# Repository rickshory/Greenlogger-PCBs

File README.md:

# Greenlogger-PCBs
Greenlogger printed circuit board files, the main board and the GPS board

For an overview:

* https://rickshory.wordpress.com/2017/08/24/greenlogger/

Format is EagleCAD schematic and board layout
 
 ## Contact
#### Developer/Company
* Project of: http://www.rickshory.com/
* e-mail: rickshory@gmail.com

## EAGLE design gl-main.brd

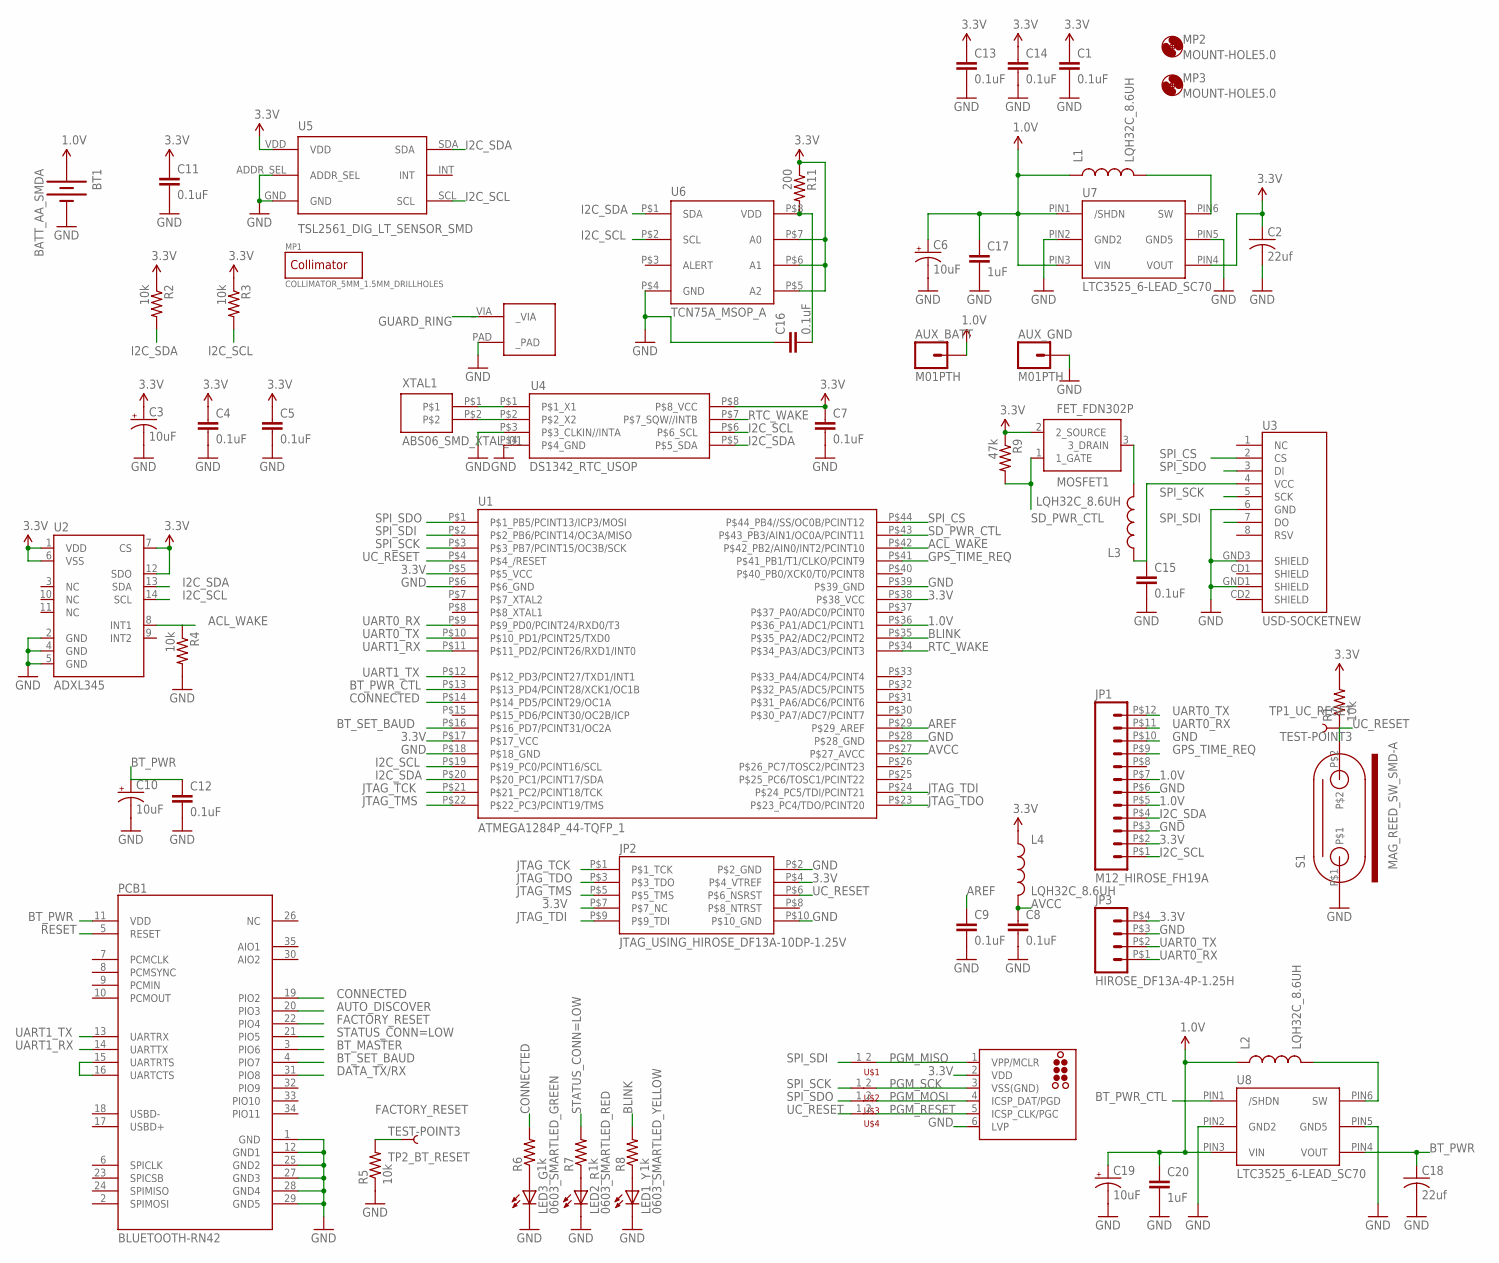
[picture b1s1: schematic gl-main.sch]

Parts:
AUX_BATT: M01PTH; 1X01
AUX_GND: M01PTH; 1X01
BT1: BATT_AA_SMDA; BATT_AA_SMD
C1, C4, C5, C7, C8, C9, C11, C12, C13, C14, C15, C16: 0.1uF; 0402-CAP
C2, C18: 22uf; C1210K
C3, C6, C10, C19: 10uF; EIA3216
C17, C20: 1uF; 0603-CAP
J1: TC2030-MCP-NL
JP1: M12_HIROSE_FH19A; HIROSE_FH19_12POS
JP2: JTAG_USING_HIROSE_DF13A-10DP-1.25V; 10PIN_MALE_HDR_DBL-ROW_HIROSE_D13
JP3: HIROSE_DF13A-4P-1.25H
L1, L2, L3, L4: LQH32C_8.6UH; 1210_SIZE_INDUCTOR
LED1_Y: 0603_SMARTLED_YELLOW; 0603_SMARTLED
LED2_R: 0603_SMARTLED_RED; 0603_SMARTLED
LED3_G: 0603_SMARTLED_GREEN; 0603_SMARTLED
MOSFET1: FET_FDN302P; SUPERSOT-3
MP1: COLLIMATOR_5MM_1.5MM_DRILLHOLES
MP2, MP3: MOUNT-HOLE5.0; 5,0
PCB1: BLUETOOTH-RN42; RN41
R1, R2, R3, R4, R5: 10k; 0402-RES
R6, R7, R8: 1k; 0402-RES
R9: 47k; 0402-RES
R11: 200; 0402-RES
S1: MAG_REED_SW_SMD-A; MAG_REED_SW_SMD_GULL-WING
TP1_UC_RESET, TP2_BT_RESET: TEST-POINT3; PAD.03X.03
U1: ATMEGA1284P_44-TQFP_1; 44-TQFP
U2: ADXL345; LGA14
U3: USD-SOCKETNEW; MICRO-SD-SOCKET-PP
U4: DS1342_RTC_USOP; 8-MICROMAX
U5: TSL2561_DIG_LT_SENSOR_SMD; 6_PAD_FLAT_NO-LEAD
U6: TCN75A_MSOP_A; MSOP-8
U7, U8: LTC3525_6-LEAD_SC70; SC70
U$1, U$2, U$3, U$4: SHORT_8MIL8MIL; SHORT_8MIL
W1: 2-SIGNAL_VIA_AND_PAD_01; 2_SIGNALS_VIA_AND_PAD
XTAL1: ABS06_SMD_XTAL_01; ABS06

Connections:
1.0V: AUX_BATT.1, BT1.P$1 (+), C6.A (+), C17.1, C19.A (+), C20.1, JP1.P$5 (5), JP1.P$7 (7), L1.P$1 (1), L2.P$1 (1), U1.P$36 (P$36_PA1/ADC1/PCINT1), U7.PIN1 (/SHDN), U7.PIN3 (VIN), U8.PIN3 (VIN)
3.3V: C1.1, C2.1, C3.A (+), C4.1, C5.1, C7.1, C11.1, C13.1, C14.1, J1.2 (VDD), JP1.P$2 (2), JP2.P$4 (P$4_VTREF), JP2.P$7 (P$7_NC), JP3.P$4 (4), L4.P$1 (1), MOSFET1.2 (2_SOURCE), R1.2, R2.1, R3.1, R9.1, R11.1, U1.P$5 (P$5_VCC), U1.P$17 (P$17_VCC), U1.P$38 (P$38_VCC), U2.1 (VDD), U2.6 (VSS), U2.7 (CS), U2.12 (SDO), U4.P$8 (P$8_VCC), U5.VDD, U6.P$5 (A2), U6.P$6 (A1), U6.P$7 (A0), U7.PIN4 (VOUT)
ACL_WAKE: R4.1, U1.P$42 (P$42_PB2/AIN0/INT2/PCINT10), U2.8 (INT1)
AREF: C9.1, U1.P$29 (P$29_AREF)
AUTO_DISCOVER: PCB1.20 (PIO3)
AVCC: C8.1, L4.P$2 (2), U1.P$27 (P$27_AVCC)
BLINK: R8.2, U1.P$35 (P$35_PA2/ADC2/PCINT2)
BT_MASTER: PCB1.3 (PIO6)
BT_PWR: C10.A (+), C12.1, C18.1, PCB1.11 (VDD), U8.PIN4 (VOUT)
BT_PWR_CTL: U1.P$13 (P$13_PD4/PCINT28/XCK1/OC1B), U8.PIN1 (/SHDN)
BT_SET_BAUD: PCB1.4 (PIO7), U1.P$16 (P$16_PD7/PCINT31/OC2A)
CONNECTED: PCB1.19 (PIO2), R6.2, U1.P$14 (P$14_PD5/PCINT29/OC1A)
DATA_TX/RX: PCB1.31 (PIO8)
FACTORY_RESET: PCB1.22 (PIO4), R5.2, TP2_BT_RESET.P$1
GND: AUX_GND.1, BT1.P$2 (-), C1.2, C2.2, C3.C (-), C4.2, C5.2, C6.C (-), C7.2, C8.2, C9.2, C10.C (-), C11.2, C12.2, C13.2, C14.2, C15.2, C16.1, C17.2, C18.2, C19.C (-), C20.2, J1.6 (LVP), JP1.P$3 (3), JP1.P$6 (6), JP1.P$10 (10), JP2.P$2 (P$2_GND), JP2.P$10 (P$10_GND), JP3.P$3 (3), LED1_Y.P$1 (C), LED2_R.P$1 (C), LED3_G.P$1 (C), PCB1.1 (GND), PCB1.12 (GND1), PCB1.25 (GND2), PCB1.27 (GND3), PCB1.28 (GND4), PCB1.29 (GND5), R4.2, R5.1, S1.P$1, U1.P$6 (P$6_GND), U1.P$18 (P$18_GND), U1.P$28 (P$28_GND), U1.P$39 (P$39_GND), U2.2 (GND), U2.4 (GND), U2.5 (GND), U3.6 (GND), U3.GND1 (SHIELD), U3.GND3 (SHIELD), U4.P$3 (P$3_CLKIN//INTA), U4.P$4 (P$4_GND), U5.ADDR_SEL, U5.GND, U6.P$4 (GND), U7.PIN2 (GND2), U7.PIN5 (GND5), U8.PIN2 (GND2), U8.PIN5 (GND5), W1.PAD (_PAD)
GPS_TIME_REQ: JP1.P$9 (9), U1.P$41 (P$41_PB1/T1/CLKO/PCINT9)
GUARD_RING: W1._VIA
I2C_SCL: JP1.P$1 (1), R3.2, U1.P$19 (P$19_PC0/PCINT16/SCL), U2.14 (SCL), U4.P$6 (P$6_SCL), U5.SCL, U6.P$2 (SCL)
I2C_SDA: JP1.P$4 (4), R2.2, U1.P$20 (P$20_PC1/PCINT17/SDA), U2.13 (SDA), U4.P$5 (P$5_SDA), U5.SDA, U6.P$1 (SDA)
JTAG_TCK: JP2.P$1 (P$1_TCK), U1.P$21 (P$21_PC2/PCINT18/TCK)
JTAG_TDI: JP2.P$9 (P$9_TDI), U1.P$24 (P$24_PC5/TDI/PCINT21)
JTAG_TDO: JP2.P$3 (P$3_TDO), U1.P$23 (P$23_PC4/TDO/PCINT20)
JTAG_TMS: JP2.P$5 (P$5_TMS), U1.P$22 (P$22_PC3/PCINT19/TMS)
unnamed: LED1_Y.P$2 (A), R8.1
unnamed: L1.P$2 (2), U7.PIN6 (SW)
unnamed: C15.1, L3.P$1 (1), U3.4 (VCC)
unnamed: L3.P$2 (2), MOSFET1.3 (3_DRAIN)
unnamed: PCB1.15 (UARTRTS), PCB1.16 (UARTCTS)
unnamed: LED2_R.P$2 (A), R7.1
unnamed: LED3_G.P$2 (A), R6.1
unnamed: C16.2, R11.2, U6.P$8 (VDD)
unnamed: L2.P$2 (2), U8.PIN6 (SW)
unnamed: U4.P$1 (P$1_X1), XTAL1.P$1
unnamed: U4.P$2 (P$2_X2), XTAL1.P$2
PGM_MISO: J1.1 (VPP/MCLR), U$1.2
PGM_MOSI: J1.4 (ICSP_DAT/PGD), U$3.2
PGM_RESET: J1.5 (ICSP_CLK/PGC), U$4.2
PGM_SCK: J1.3 (VSS(GND)), U$2.2
RESET: PCB1.5 (RESET)
RTC_WAKE: U1.P$34 (P$34_PA3/ADC3/PCINT3), U4.P$7 (P$7_SQW//INTB)
SD_PWR_CTL: MOSFET1.1 (1_GATE), R9.2, U1.P$43 (P$43_PB3/AIN1/OC0A/PCINT11)
SPI_CS: U1.P$44 (P$44_PB4//SS/OC0B/PCINT12), U3.2 (CS)
SPI_SCK: U1.P$3 (P$3_PB7/PCINT15/OC3B/SCK), U3.5 (SCK), U$2.1
SPI_SDI: U1.P$2 (P$2_PB6/PCINT14/OC3A/MISO), U3.7 (DO), U$1.1
SPI_SDO: U1.P$1 (P$1_PB5/PCINT13/ICP3/MOSI), U3.3 (DI), U$3.1
STATUS_CONN=LOW: PCB1.21 (PIO5), R7.2
UART0_RX: JP1.P$11 (11), JP3.P$1 (1), U1.P$9 (P$9_PD0/PCINT24/RXD0/T3)
UART0_TX: JP1.P$12 (12), JP3.P$2 (2), U1.P$10 (P$10_PD1/PCINT25/TXD0)
UART1_RX: PCB1.14 (UARTTX), U1.P$11 (P$11_PD2/PCINT26/RXD1/INT0)
UART1_TX: PCB1.13 (UARTRX), U1.P$12 (P$12_PD3/PCINT27/TXD1/INT1)
UC_RESET: JP2.P$6 (P$6_NSRST), R1.1, S1.P$2, TP1_UC_RESET.P$1, U1.P$4 (P$4_/RESET), U$4.1

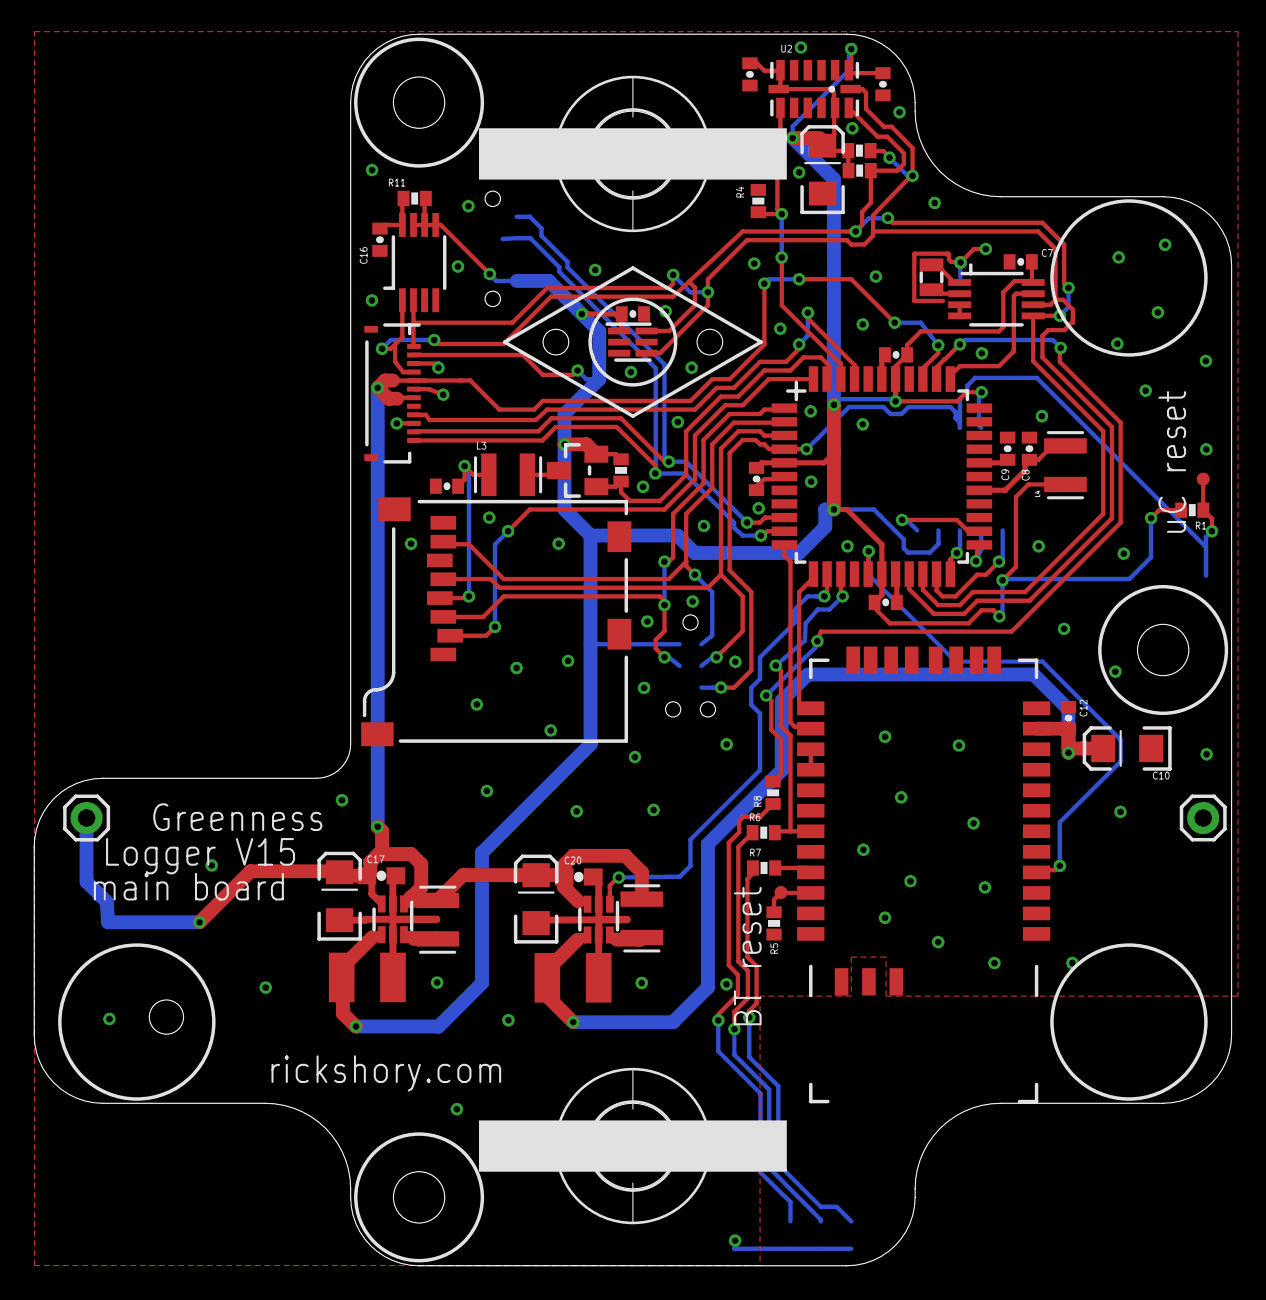
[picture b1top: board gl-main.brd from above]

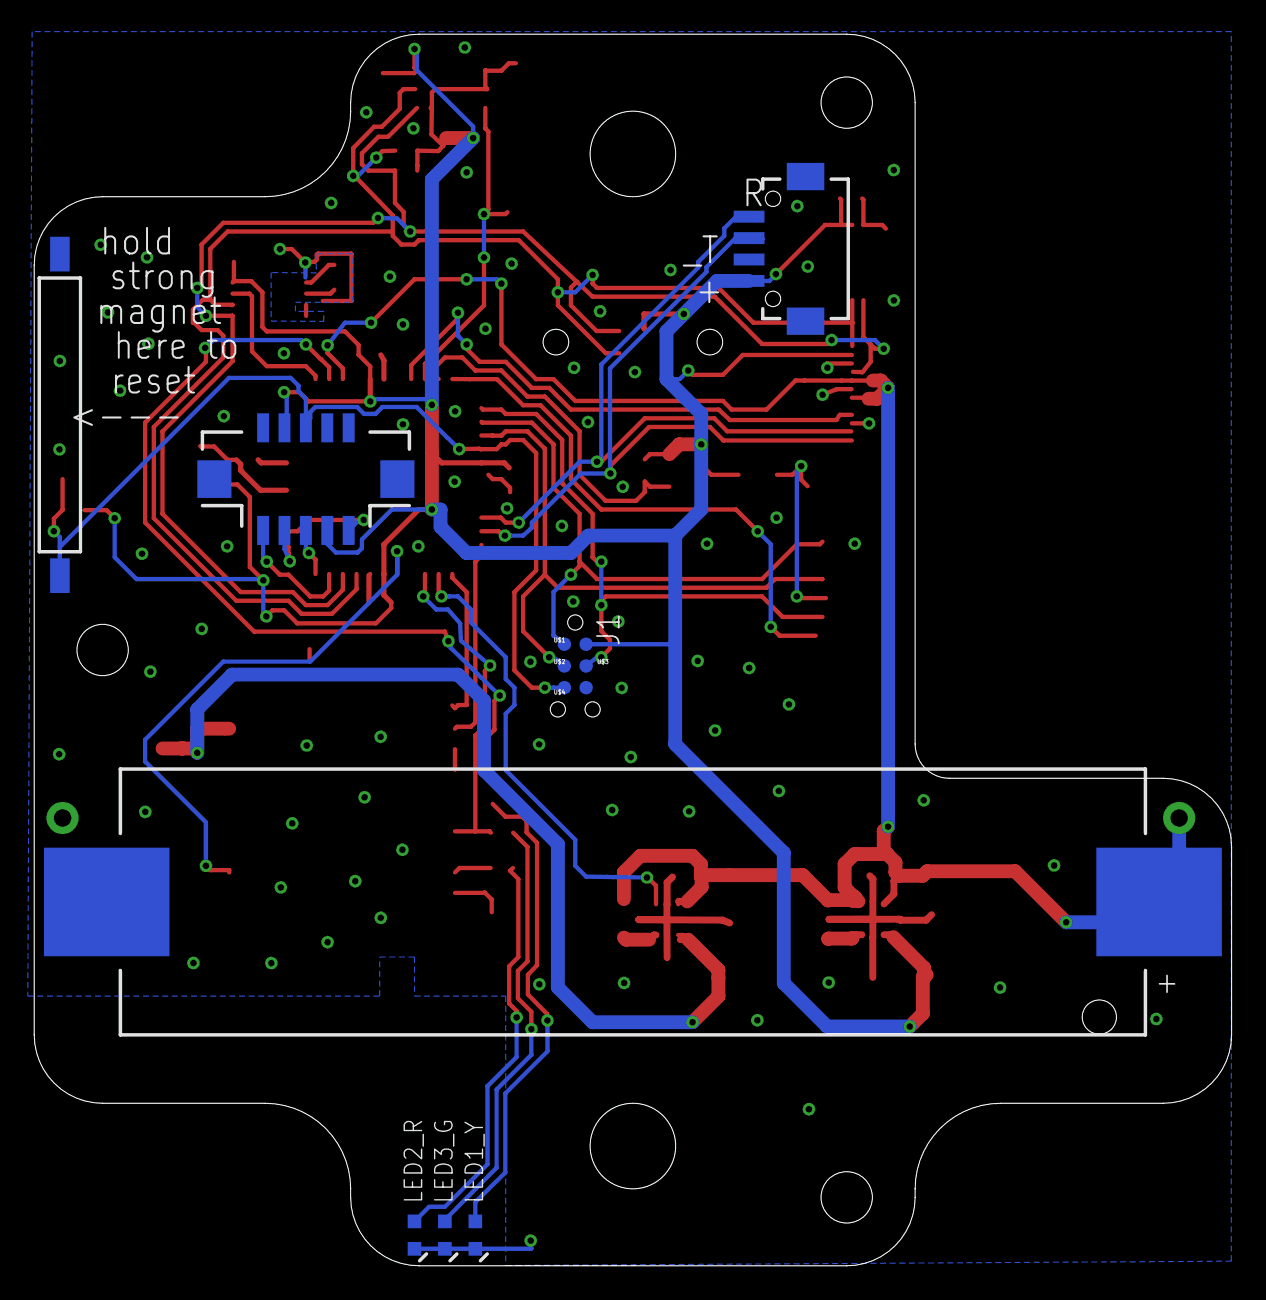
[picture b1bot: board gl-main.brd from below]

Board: 2 copper layers, 70.0 x 72.0 mm, 66 parts (12 on the bottom side), 46 nets.

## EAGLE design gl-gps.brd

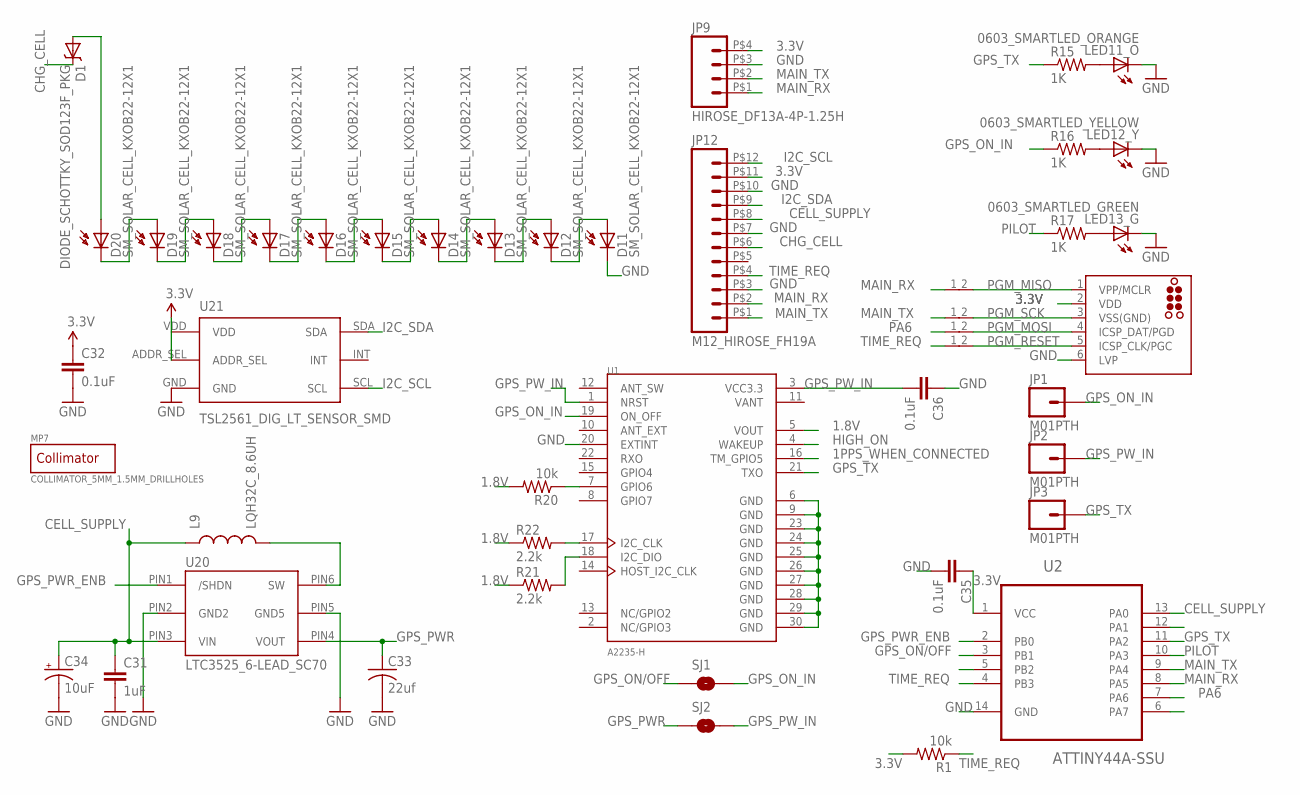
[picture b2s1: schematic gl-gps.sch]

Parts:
C31: 1uF; 0603-CAP
C32, C35, C36: 0.1uF; 0402-CAP
C33: 22uf; C1210K
C34: 10uF; EIA3216
D1: DIODE_SCHOTTKY_SOD123F_PKG; SOD123F
D11, D12, D13, D14, D15, D16, D17, D18, D19, D20: SM_SOLAR_CELL_KXOB22-12X1
J1: TC2030-MCP-NL
JP1, JP2, JP3: M01PTH; 1X01
JP9: HIROSE_DF13A-4P-1.25H
JP12: M12_HIROSE_FH19A; HIROSE_FH19_12POS
L9: LQH32C_8.6UH; 1210_SIZE_INDUCTOR
LED11_O: 0603_SMARTLED_ORANGE; 0603_SMARTLED
LED12_Y: 0603_SMARTLED_YELLOW; 0603_SMARTLED
LED13_G: 0603_SMARTLED_GREEN; 0603_SMARTLED
MP7: COLLIMATOR_5MM_1.5MM_DRILLHOLES
R1, R20: 10k; 0402-RES
R15, R16, R17: 1K; 0402-RES
R21, R22: 2.2k; 0402-RES
SJ1, SJ2: SOLDERJUMPERTRACE; SJ_2S-TRACE
U1: A2235-H; XCVR_A2235-H
U2: ATTINY44A-SSU; SOIC127P600X175-14N
U20: LTC3525_6-LEAD_SC70; SC70
U21: TSL2561_DIG_LT_SENSOR_SMD; 6_PAD_FLAT_NO-LEAD
U$2, U$3, U$4, U$5: SHORT_8MIL8MIL; SHORT_8MIL

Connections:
1.8V: R20.2, R21.1, R22.1, U1.5 (VOUT)
1PPS_WHEN_CONNECTED: U1.16 (TM_GPIO5)
3.3V: C32.1, C35.1, J1.2 (VDD), JP9.P$4 (4), JP12.P$11 (11), R1.2, U2.1 (VCC), U21.ADDR_SEL, U21.VDD
CELL_SUPPLY: C31.1, C34.A (+), JP12.P$8 (8), L9.P$1 (1), U2.13 (PA0), U20.PIN3 (VIN)
CHG_CELL: D1.P$1 (C), JP12.P$6 (6)
GND: C31.2, C32.2, C33.2, C34.C (-), C35.2, C36.1, D11.CATHODE (C), J1.6 (LVP), JP9.P$3 (3), JP12.P$3 (3), JP12.P$7 (7), JP12.P$10 (10), LED11_O.P$1 (C), LED12_Y.P$1 (C), LED13_G.P$1 (C), U1.6 (GND), U1.9 (GND), U1.20 (EXTINT), U1.23 (GND), U1.24 (GND), U1.25 (GND), U1.26 (GND), U1.27 (GND), U1.28 (GND), U1.29 (GND), U1.30 (GND), U2.14 (GND), U20.PIN2 (GND2), U20.PIN5 (GND5), U21.GND
GPS_ON/OFF: SJ1.1, U2.3 (PB1)
GPS_ON_IN: JP1.1, R16.1, SJ1.2, U1.19 (ON_OFF)
GPS_PWR: C33.1, SJ2.1, U20.PIN4 (VOUT)
GPS_PWR_ENB: U2.2 (PB0), U20.PIN1 (/SHDN)
GPS_PW_IN: C36.2, JP2.1, SJ2.2, U1.1 (NRST), U1.3 (VCC3.3)
GPS_TX: JP3.1, R15.1, U1.21 (TXO), U2.11 (PA2)
HIGH_ON: U1.4 (WAKEUP)
I2C_SCL: JP12.P$12 (12), U21.SCL
I2C_SDA: JP12.P$9 (9), U21.SDA
MAIN_RX: JP9.P$1 (1), JP12.P$2 (2), U2.8 (PA5), U$2.1
MAIN_TX: JP9.P$2 (2), JP12.P$1 (1), U2.9 (PA4), U$3.1
unnamed: D19.ANODE (A), D20.CATHODE (C)
unnamed: D17.ANODE (A), D18.CATHODE (C)
unnamed: D15.ANODE (A), D16.CATHODE (C)
unnamed: D1.P$2 (A), D20.ANODE (A)
unnamed: D18.ANODE (A), D19.CATHODE (C)
unnamed: D16.ANODE (A), D17.CATHODE (C)
unnamed: D14.ANODE (A), D15.CATHODE (C)
unnamed: D12.ANODE (A), D13.CATHODE (C)
unnamed: LED11_O.P$2 (A), R15.2
unnamed: D13.ANODE (A), D14.CATHODE (C)
unnamed: L9.P$2 (2), U20.PIN6 (SW)
unnamed: D11.ANODE (A), D12.CATHODE (C)
unnamed: LED12_Y.P$2 (A), R16.2
unnamed: LED13_G.P$2 (A), R17.2
unnamed: R21.2, U1.18 (I2C_DIO)
unnamed: R22.2, U1.17 (I2C_CLK)
unnamed: R20.1, U1.7 (GPIO6)
PA6: U2.7 (PA6), U$4.1
PGM_MISO: J1.1 (VPP/MCLR), U$2.2
PGM_MOSI: J1.4 (ICSP_DAT/PGD), U$4.2
PGM_RESET: J1.5 (ICSP_CLK/PGC), U$5.2
PGM_SCK: J1.3 (VSS(GND)), U$3.2
PILOT: R17.1, U2.10 (PA3)
TIME_REQ: JP12.P$4 (4), R1.1, U2.4 (PB3), U$5.1
VANT: U1.11 (VANT)

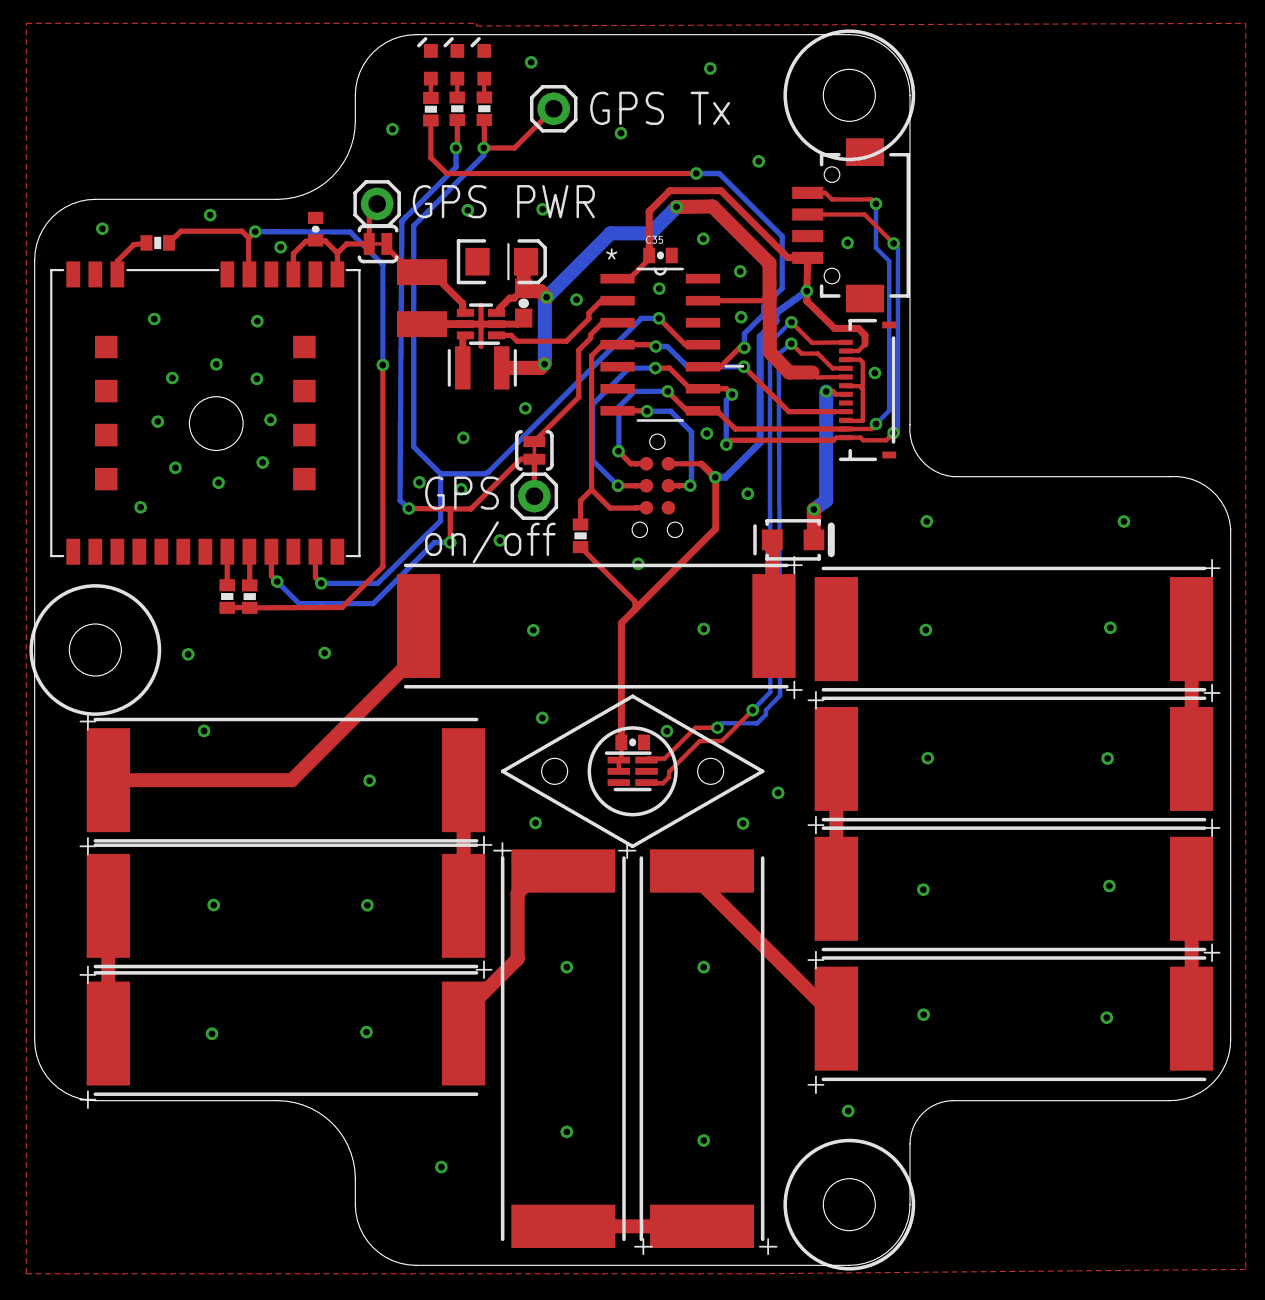
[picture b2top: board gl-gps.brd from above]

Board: 2 copper layers, 69.0 x 71.0 mm, 45 parts (0 on the bottom side), 39 nets.

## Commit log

2018-08-10 Update README.md
    putting these public
2018-08-10 making these public, version 15

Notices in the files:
parts and their libraries:
tag-connect: ©2009 ROFA.cz - modified and updated by Robert Darlington ‹rdarlington@gmail.com›
